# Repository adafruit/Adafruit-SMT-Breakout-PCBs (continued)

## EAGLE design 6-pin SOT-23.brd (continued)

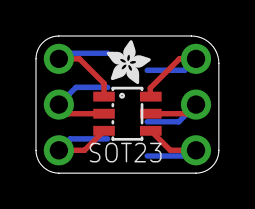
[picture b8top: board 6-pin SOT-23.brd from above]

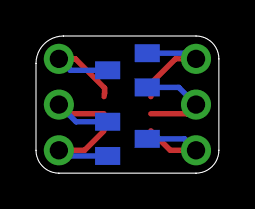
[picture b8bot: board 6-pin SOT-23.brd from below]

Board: 2 copper layers, 10.2 x 7.6 mm, 6 parts (2 on the bottom side), 6 nets.

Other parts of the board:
U$2: ADAFRUIT_2.5MM
